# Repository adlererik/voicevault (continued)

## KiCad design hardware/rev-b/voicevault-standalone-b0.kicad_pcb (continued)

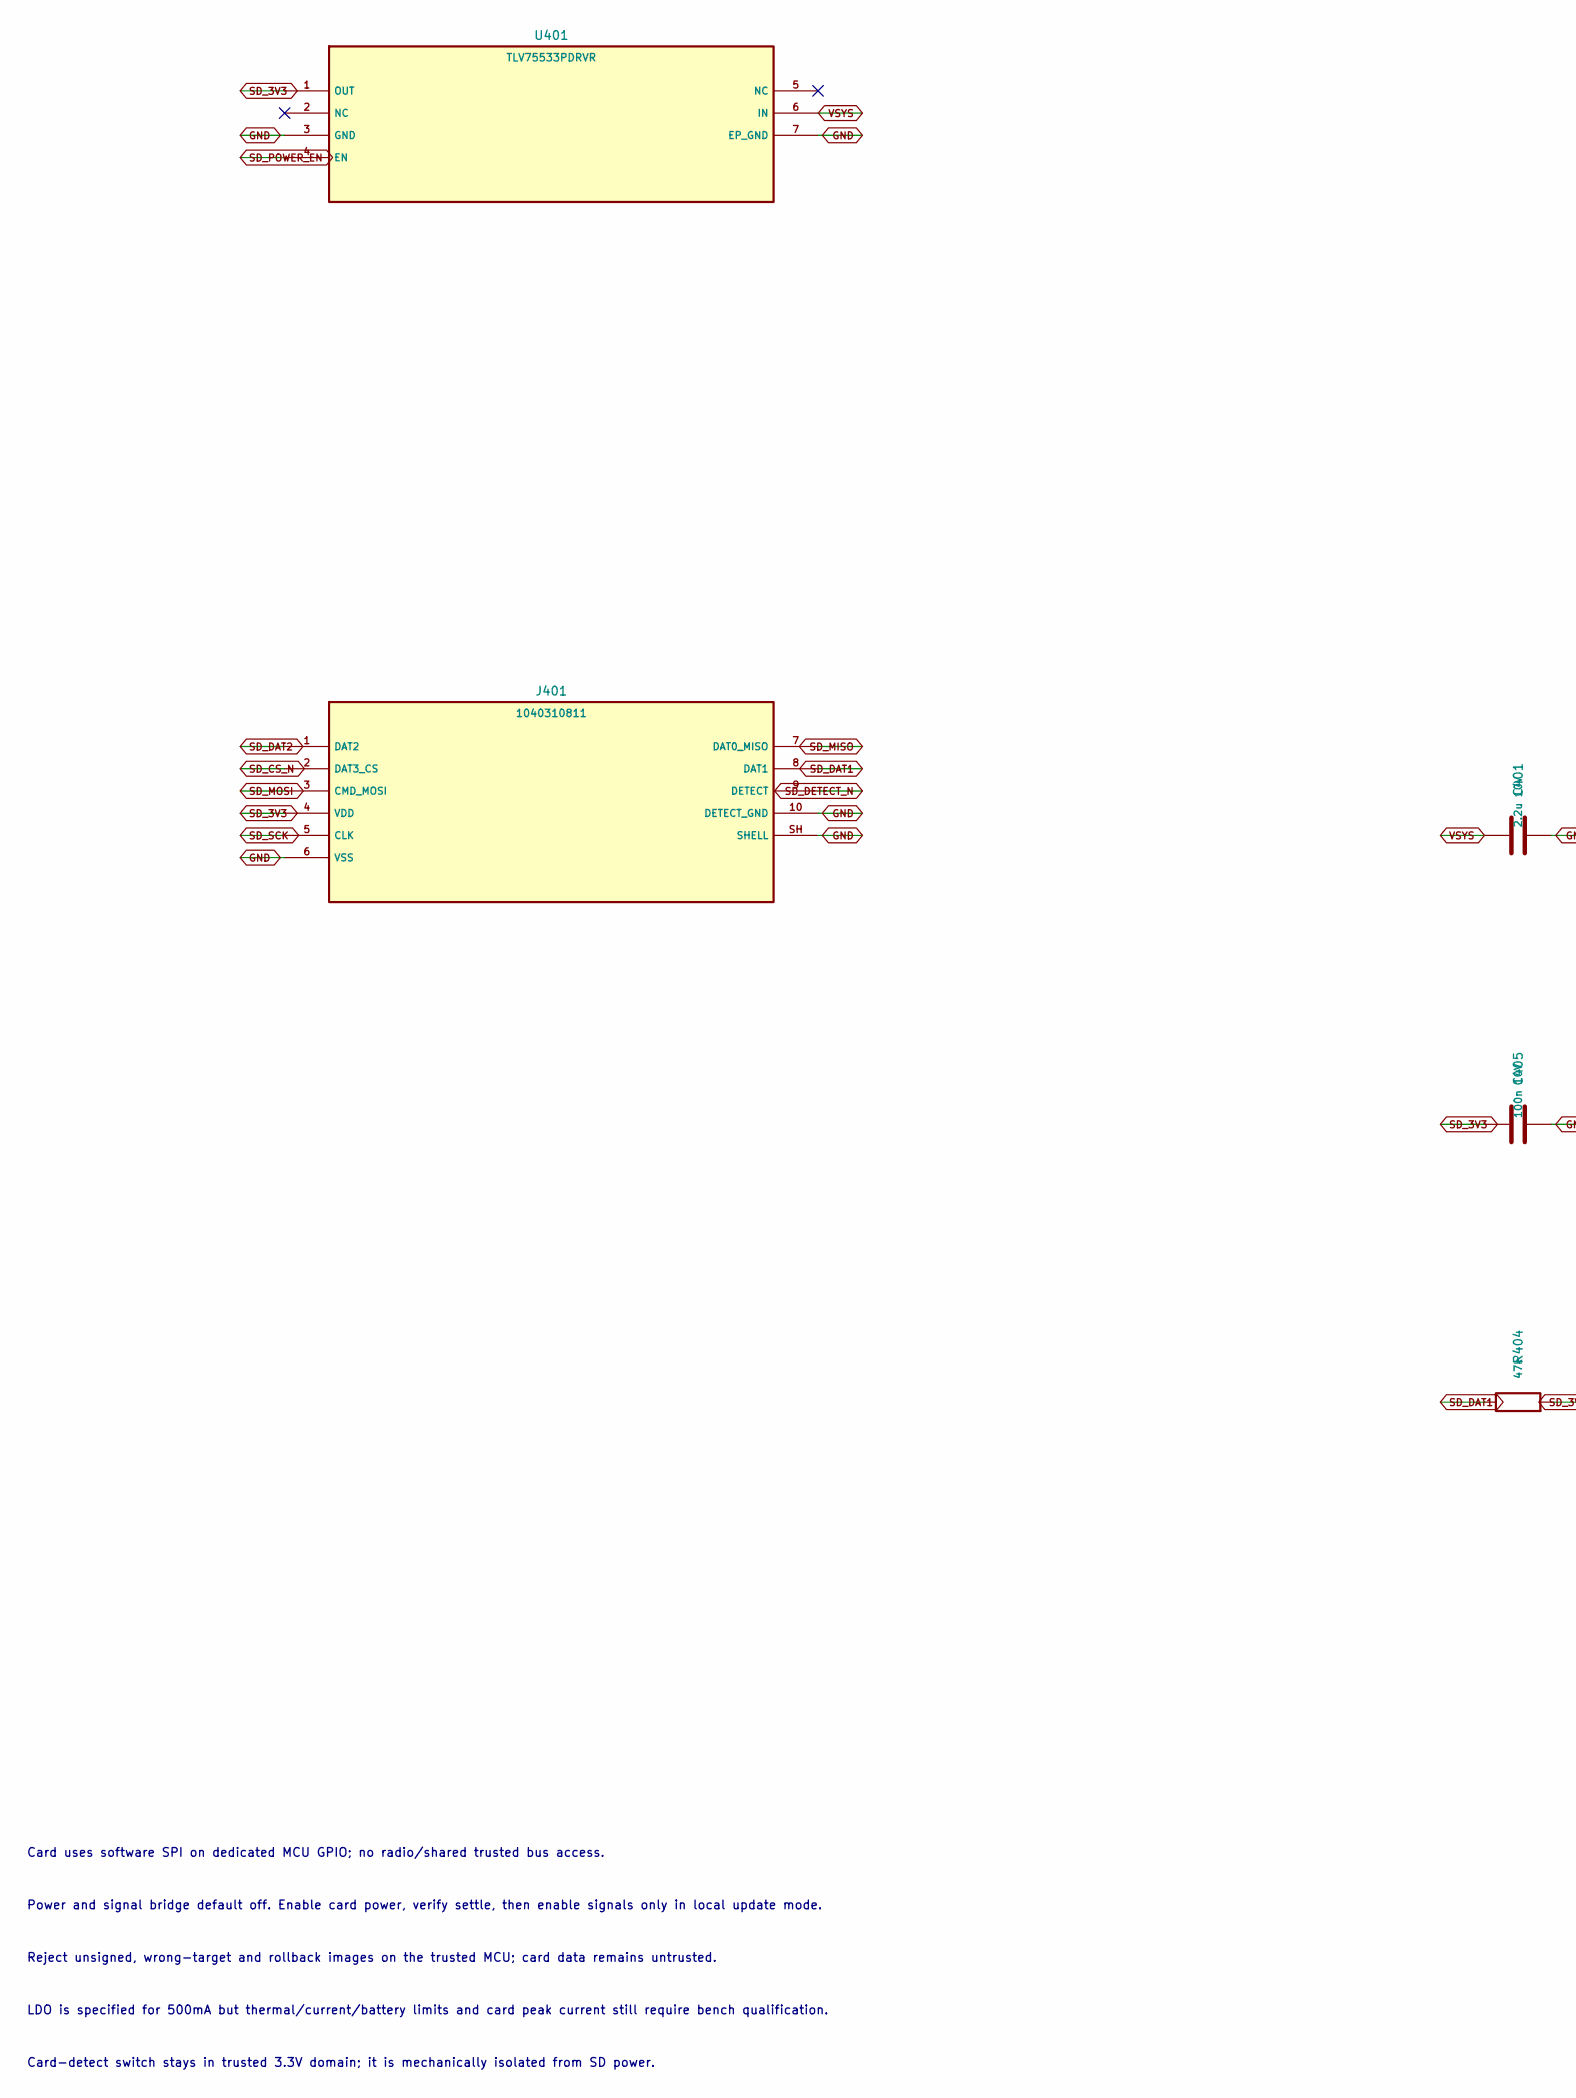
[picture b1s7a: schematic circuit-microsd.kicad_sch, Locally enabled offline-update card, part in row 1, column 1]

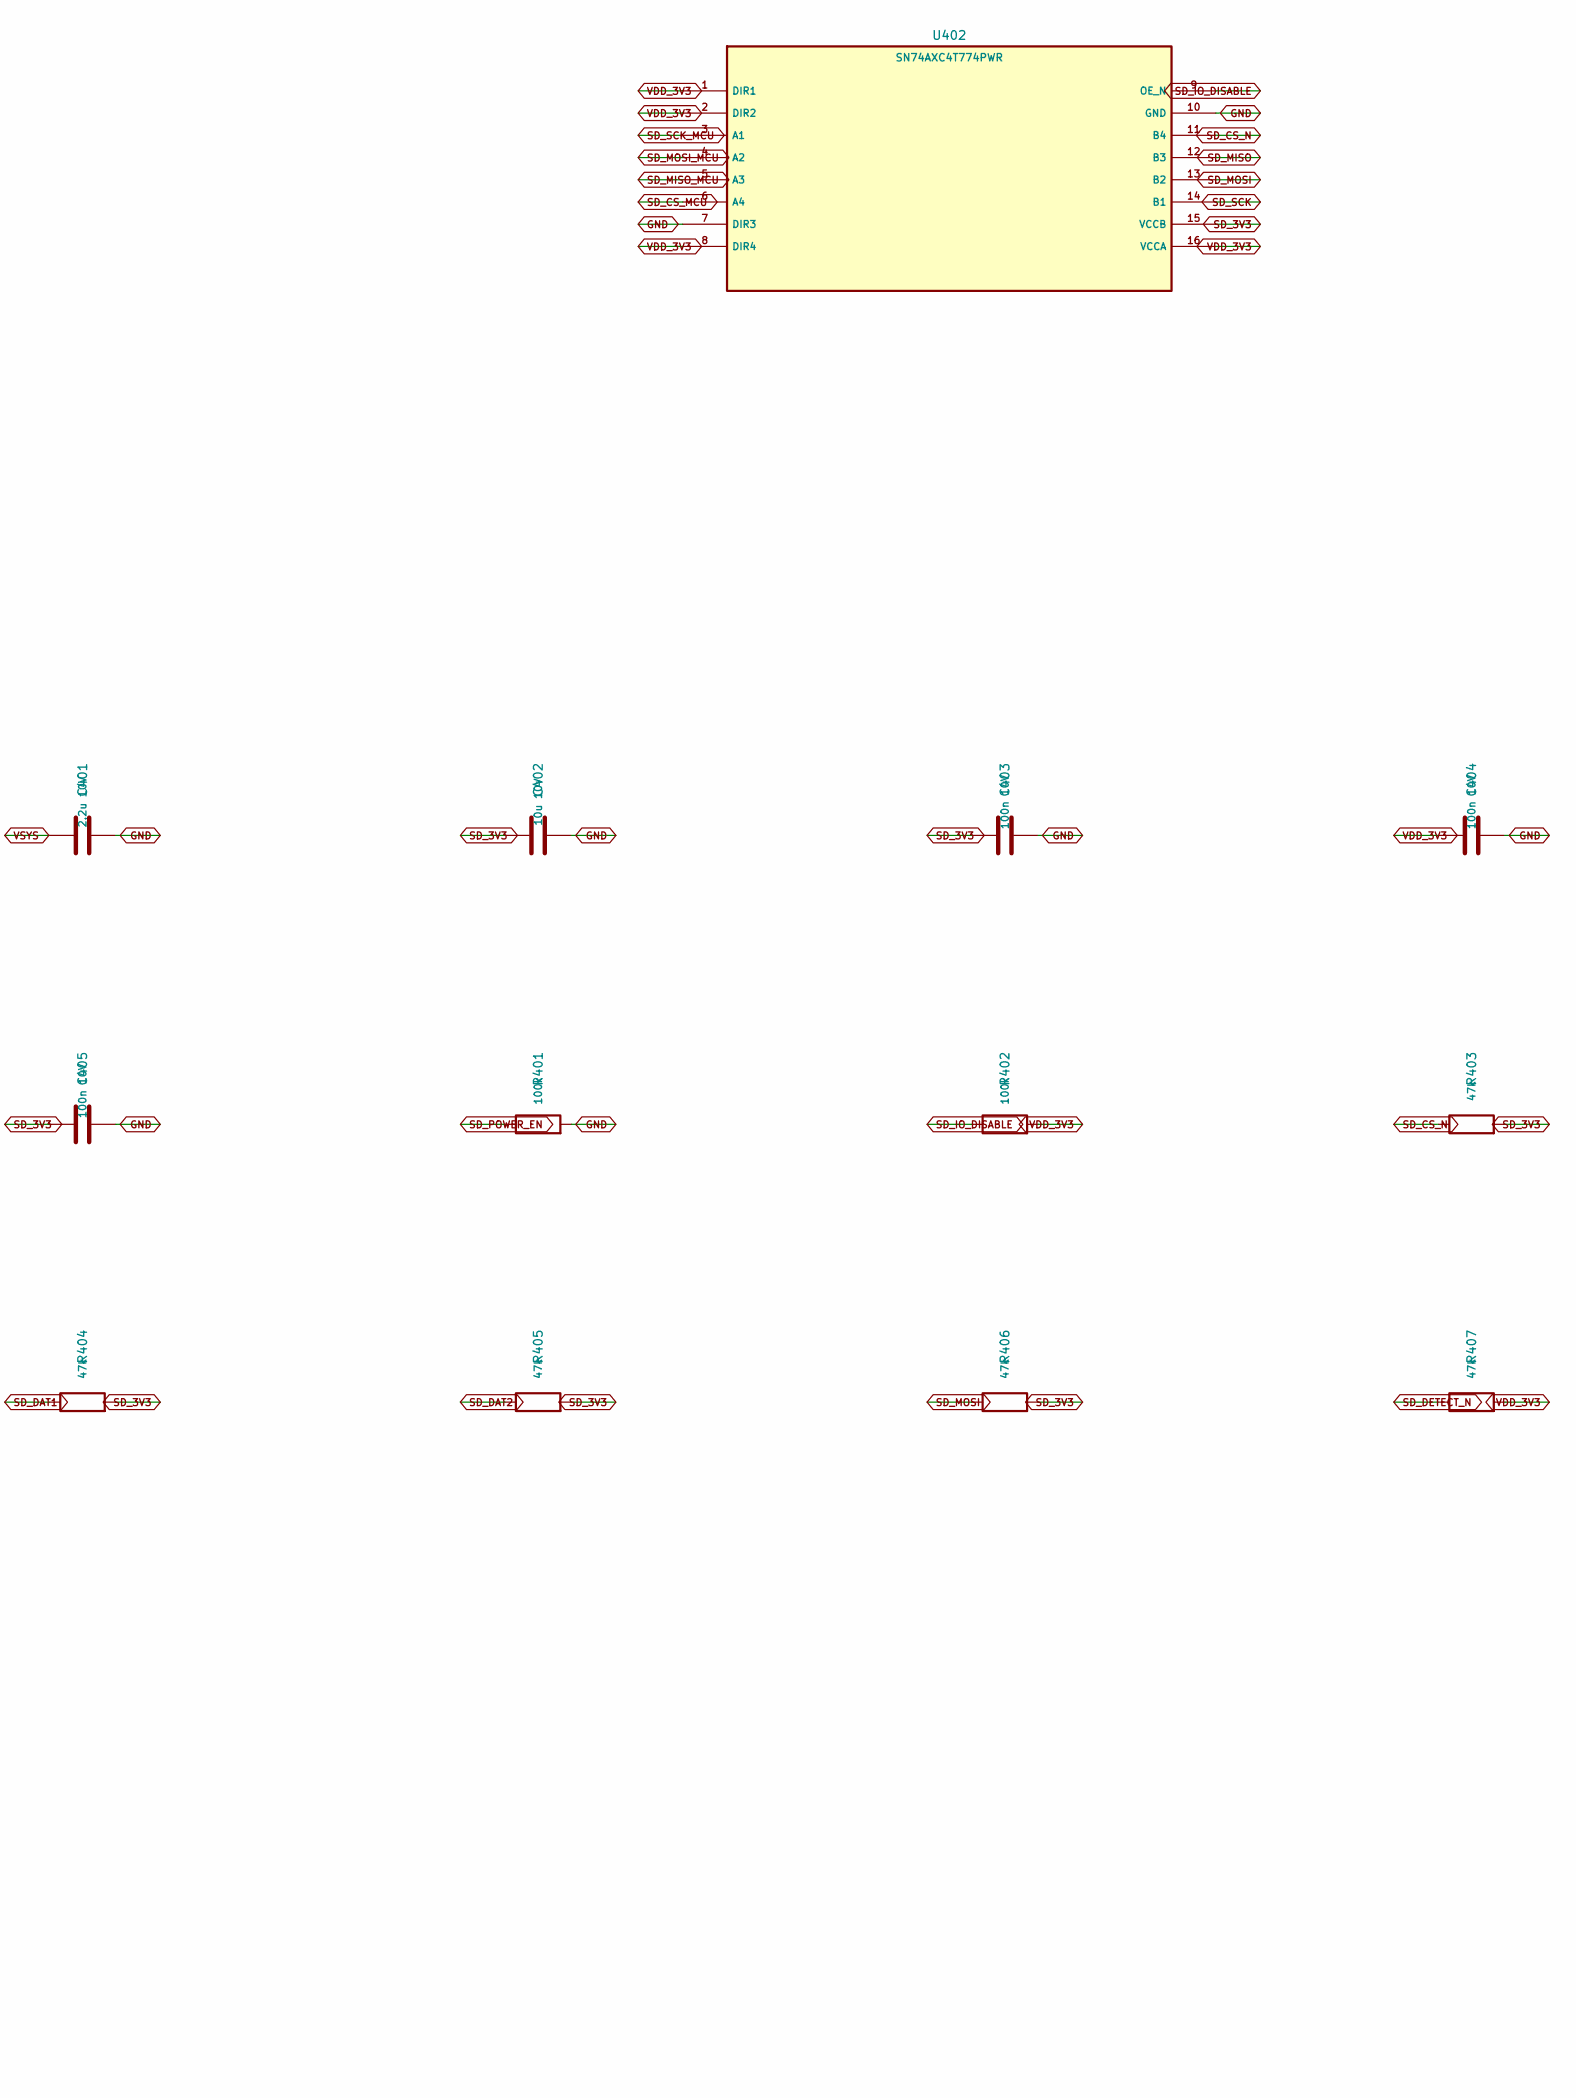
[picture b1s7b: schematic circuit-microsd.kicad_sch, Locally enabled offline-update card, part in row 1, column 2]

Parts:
C401: 2.2u 10V; C_0603_1608Metric
C402: 10u 10V; C_0805_2012Metric
C403, C404, C405: 100n 10V; C_0402_1005Metric
J401: 1040310811; microSD_HC_Molex_104031-0811
R401, R402: 100k; R_0402_1005Metric
R403, R404, R405, R406, R407: 47k; R_0402_1005Metric
U401: TLV75533PDRVR; TI_DRV0006A_WSON6_2x2_EP1x1p6
U402: SN74AXC4T774PWR; TSSOP-16_4.4x5mm_P0.65mm

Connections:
GND: C401.2, C402.2, C403.2, C404.2, C405.2, J401.6 (VSS), J401.10 (DETECT_GND), J401.SH (SHELL), R401.2, U401.3 (GND), U401.7 (EP_GND), U402.7 (DIR3), U402.10 (GND); also elsewhere on the board
SD_3V3: C402.1, C403.1, C405.1, J401.4 (VDD), R403.2, R404.2, R405.2, R406.2, U401.1 (OUT), U402.15 (VCCB); also elsewhere on the board
SD_CS_MCU: U402.6 (A4); also elsewhere on the board
SD_CS_N: J401.2 (DAT3_CS), R403.1, U402.11 (B4)
SD_DAT1: J401.8 (DAT1), R404.1
SD_DAT2: J401.1 (DAT2), R405.1
SD_DETECT_N: J401.9 (DETECT), R407.1; also elsewhere on the board
SD_IO_DISABLE: R402.1, U402.9 (OE_N); also elsewhere on the board
SD_MISO: J401.7 (DAT0_MISO), U402.12 (B3)
SD_MISO_MCU: U402.5 (A3); also elsewhere on the board
SD_MOSI: J401.3 (CMD_MOSI), R406.1, U402.13 (B2)
SD_MOSI_MCU: U402.4 (A2); also elsewhere on the board
SD_POWER_EN: R401.1, U401.4 (EN); also elsewhere on the board
SD_SCK: J401.5 (CLK), U402.14 (B1)
SD_SCK_MCU: U402.3 (A1); also elsewhere on the board
VDD_3V3: C404.1, R402.2, R407.2, U402.1 (DIR1), U402.2 (DIR2), U402.8 (DIR4), U402.16 (VCCA); also elsewhere on the board
VSYS: C401.1, U401.6 (IN); also elsewhere on the board

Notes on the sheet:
Card uses software SPI on dedicated MCU GPIO; no radio/shared trusted bus access.
Power and signal bridge default off. Enable card power, verify settle, then enable signals only in local update mode.
Reject unsigned, wrong-target and rollback images on the trusted MCU; card data remains untrusted.
LDO is specified for 500mA but thermal/current/battery limits and card peak current still require bench qualification.
Card-detect switch stays in trusted 3.3V domain; it is mechanically isolated from SD power.

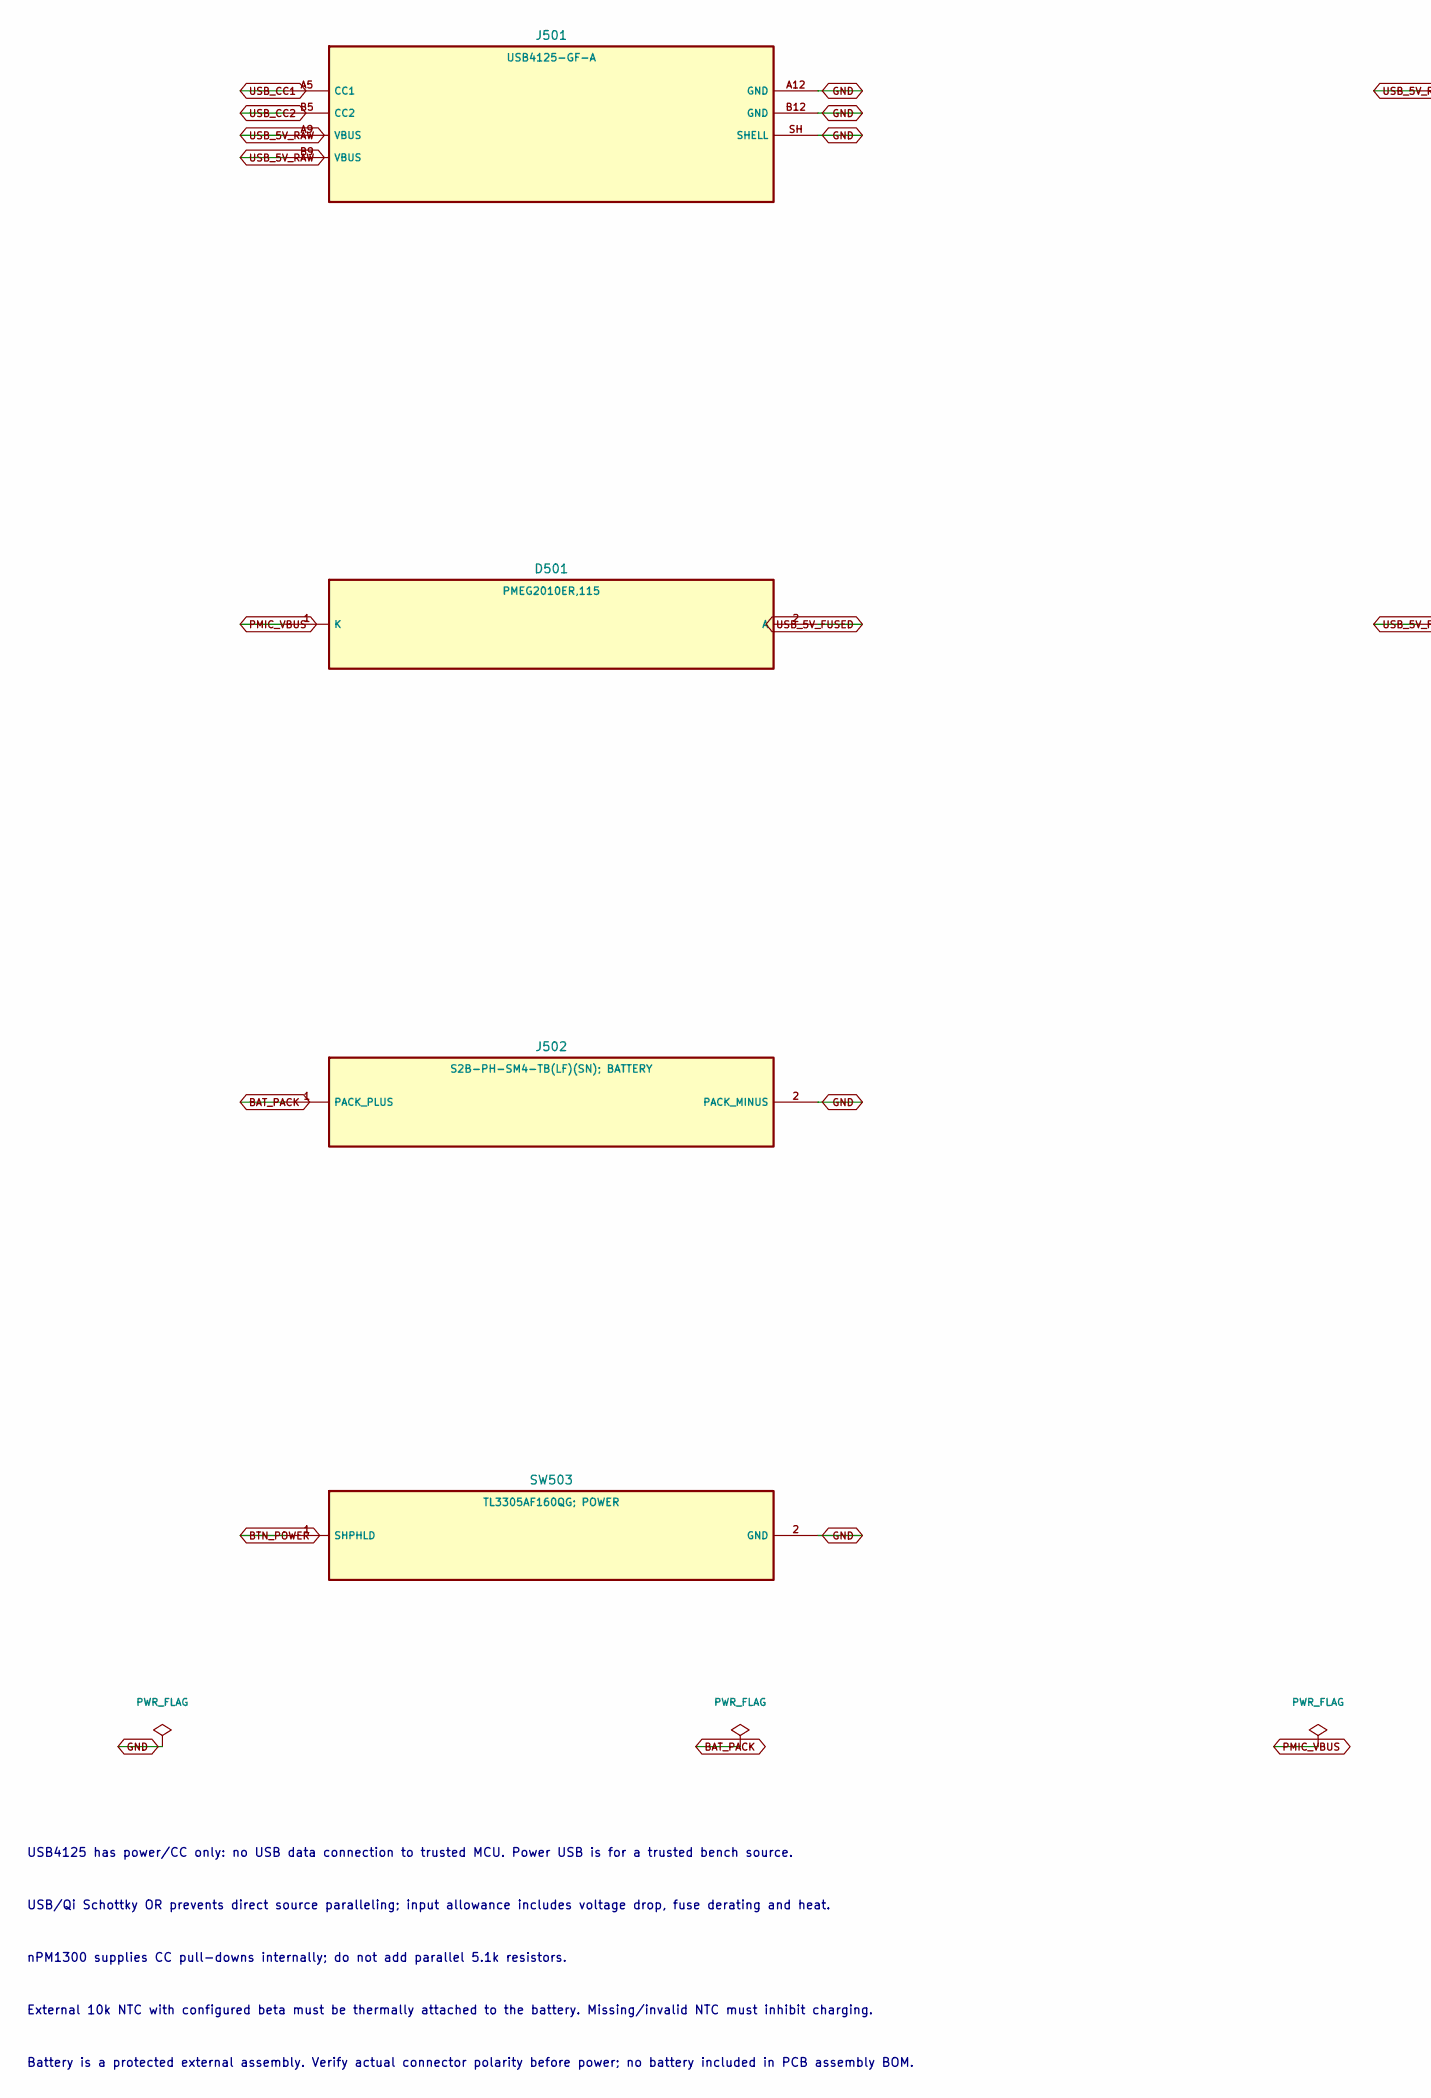
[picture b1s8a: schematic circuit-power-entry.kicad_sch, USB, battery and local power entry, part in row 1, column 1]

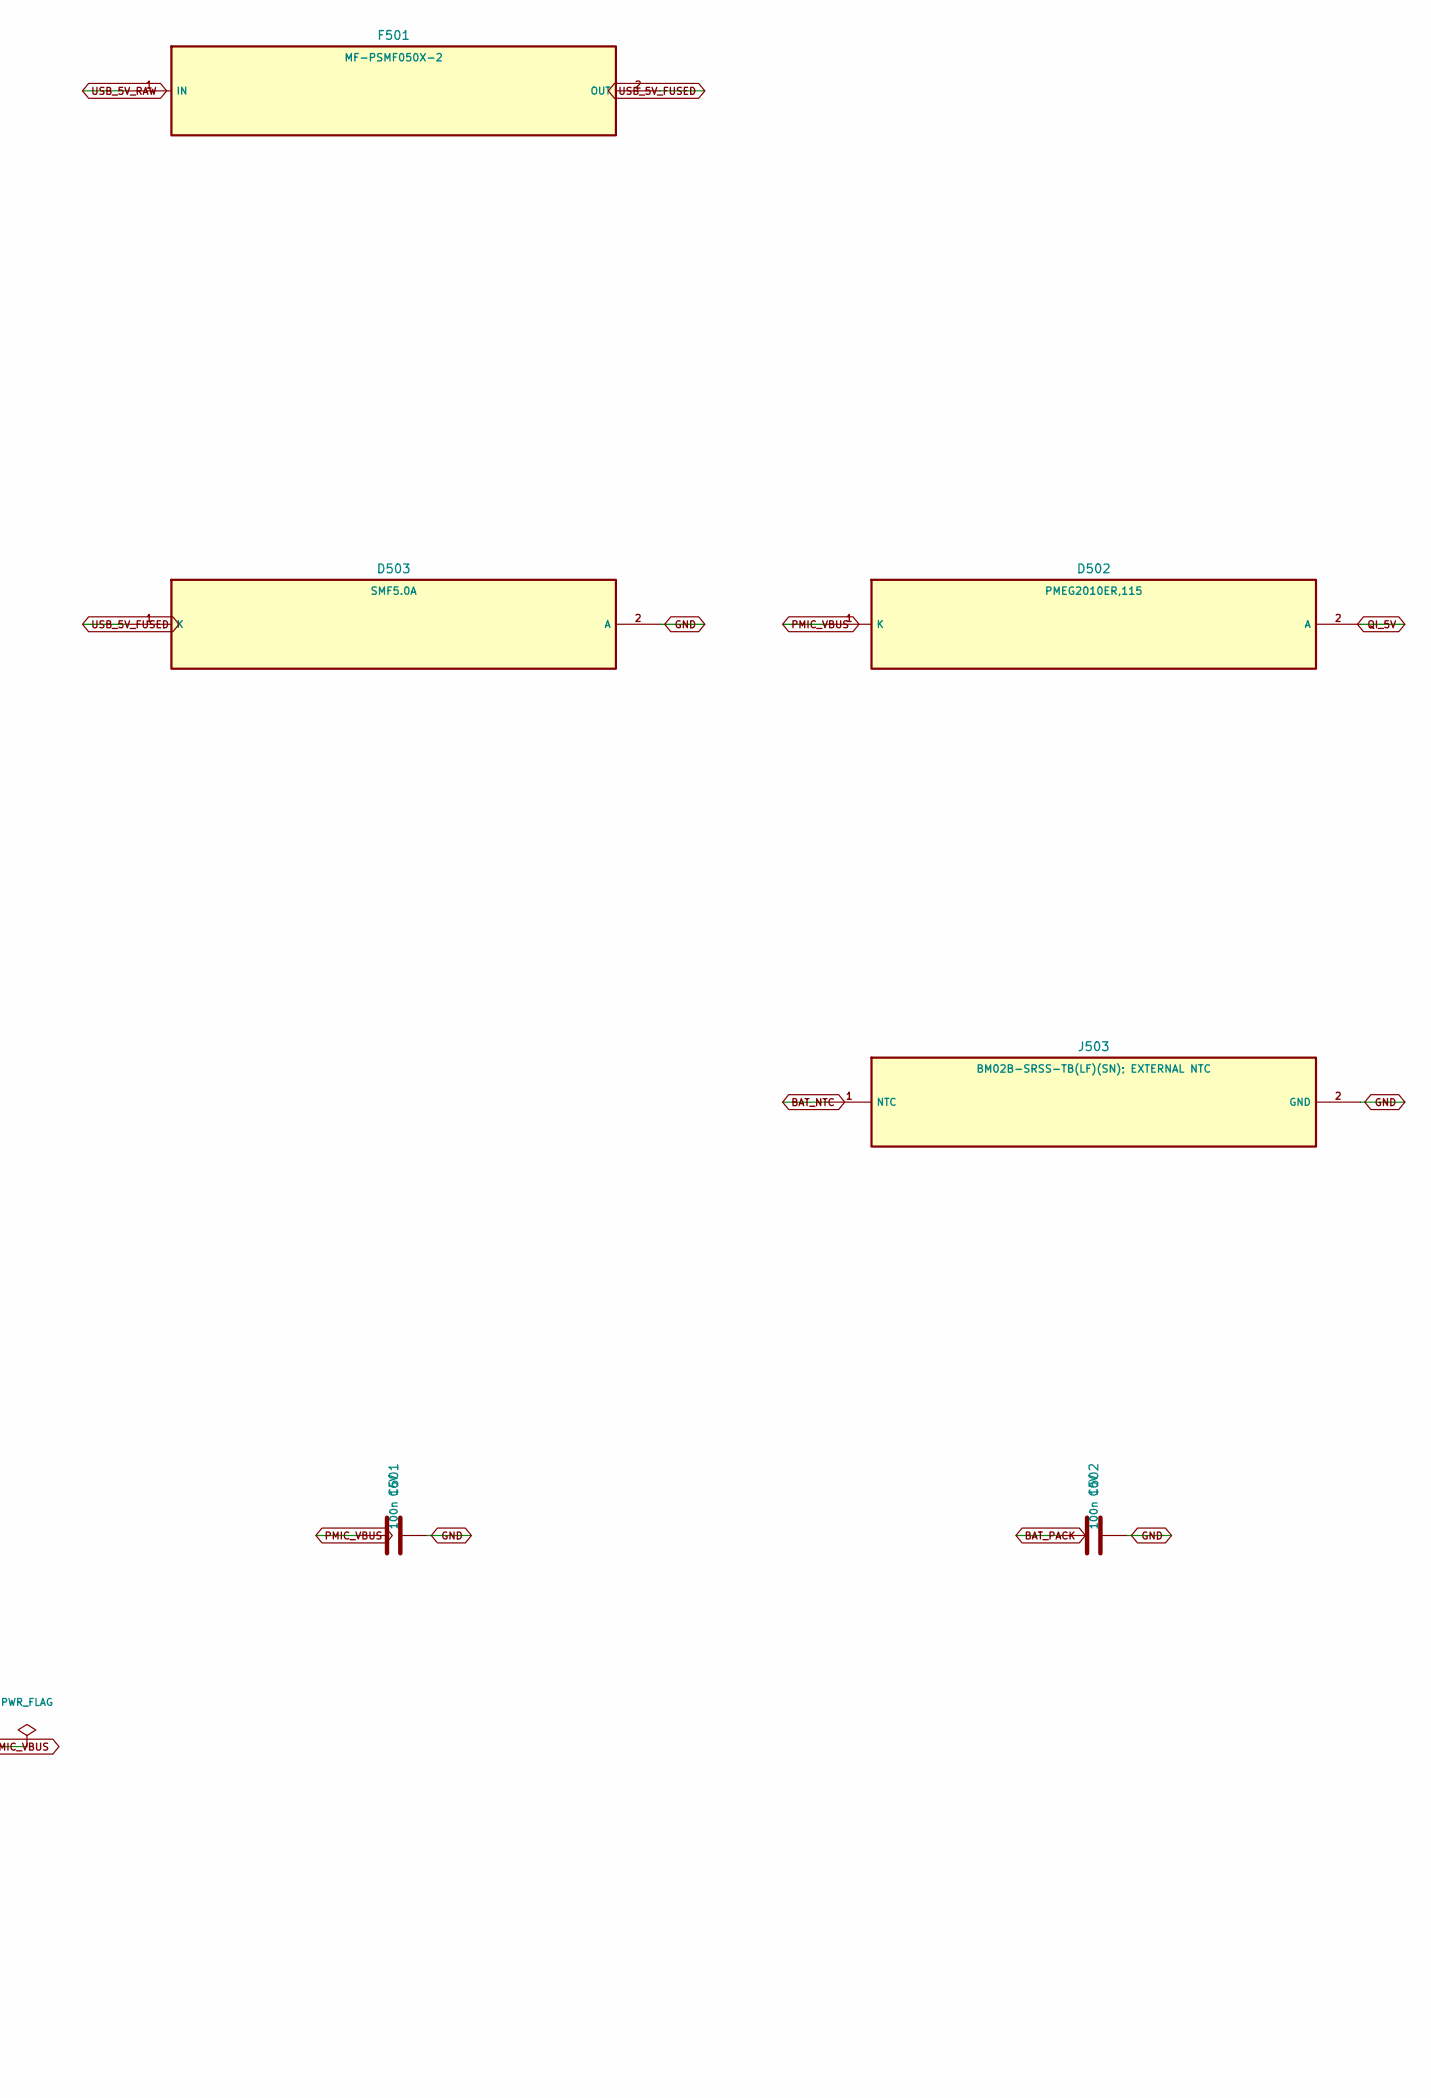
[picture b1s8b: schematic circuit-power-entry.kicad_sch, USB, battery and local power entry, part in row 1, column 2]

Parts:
C501: 100n 16V; C_0402_1005Metric
C502: 100n 10V; C_0402_1005Metric
D501, D502: PMEG2010ER,115; Nexperia_CFP3_SOD-123W
D503: SMF5.0A; D_SOD-123F
F501: MF-PSMF050X-2; Fuse_0805_2012Metric
J501: USB4125-GF-A; USB_C_Receptacle_GCT_USB4125-xx-x_6P_TopMnt_Horizontal
J502: S2B-PH-SM4-TB(LF)(SN); BATTERY; JST_PH_S2B-PH-SM4-TB_1x02-1MP_P2.00mm_Horizontal
J503: BM02B-SRSS-TB(LF)(SN); EXTERNAL NTC; JST_SH_BM02B-SRSS-TB_1x02-1MP_P1.00mm_Vertical
SW503: TL3305AF160QG; POWER; SW_SPST_TL3305A

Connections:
BAT_NTC: J503.1 (NTC); also elsewhere on the board
BAT_PACK: C502.1, J502.1 (PACK_PLUS); also elsewhere on the board
BTN_POWER: SW503.1 (SHPHLD); also elsewhere on the board
GND: C501.2, C502.2, D503.2 (A), J501.A12 (GND), J501.B12 (GND), J501.SH (SHELL), J502.2 (PACK_MINUS), J503.2 (GND), SW503.2 (GND); also elsewhere on the board
PMIC_VBUS: C501.1, D501.1 (K), D502.1 (K); also elsewhere on the board
QI_5V: D502.2 (A); also elsewhere on the board
USB_5V_FUSED: D501.2 (A), D503.1 (K), F501.2 (OUT)
USB_5V_RAW: F501.1 (IN), J501.A9 (VBUS), J501.B9 (VBUS)
USB_CC1: J501.A5 (CC1); also elsewhere on the board
USB_CC2: J501.B5 (CC2); also elsewhere on the board

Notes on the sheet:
USB4125 has power/CC only: no USB data connection to trusted MCU. Power USB is for a trusted bench source.
USB/Qi Schottky OR prevents direct source paralleling; input allowance includes voltage drop, fuse derating and heat.
nPM1300 supplies CC pull-downs internally; do not add parallel 5.1k resistors.
External 10k NTC with configured beta must be thermally attached to the battery. Missing/invalid NTC must inhibit charging.
Battery is a protected external assembly. Verify actual connector polarity before power; no battery included in PCB assembly BOM.

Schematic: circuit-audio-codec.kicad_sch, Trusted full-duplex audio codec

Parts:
C601, C602, C603, C605: 10u 10V; C_0805_2012Metric
C604, C606, C607, C608: 100n 10V; C_0402_1005Metric
D601: BAT54WS; DLDO to ALDO pop suppression; D_SOD-323
R601, R602: 2.2k; R_0402_1005Metric
R603: 100k; R_0402_1005Metric
U601: TLV320AIC3204IRHBR; QFN-32-1EP_5x5mm_P0.5mm_EP3.45x3.45mm

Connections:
AUD_ADC_DATA: U601.5 (DOUT); also elsewhere on the board
AUD_AVDD_1V8: C601.1, C607.1, D601.1 (K), U601.24 (AVDD_ALDO_OUT)
AUD_BCLK: U601.2 (BCLK); also elsewhere on the board
AUD_DAC_DATA: U601.4 (DIN); also elsewhere on the board
AUD_DVDD_1V72: C602.1, C608.1, D601.2 (A), U601.29 (DVDD_DLDO_OUT)
AUD_HPL_DC: U601.25 (HPL); also elsewhere on the board
AUD_HPR_DC: U601.27 (HPR); also elsewhere on the board
AUD_LDOIN_3V3: C605.1, C606.1, U601.26 (LDOIN_HPVDD); also elsewhere on the board
AUD_MCLK: U601.1 (MCLK); also elsewhere on the board
AUD_MICBIAS: U601.19 (MICBIAS); also elsewhere on the board
AUD_REF: C603.1, U601.18 (REF)
AUD_RESET_N: R603.1, U601.31 (RESET_N); also elsewhere on the board
AUD_SCL: R601.1, U601.9 (SCL); also elsewhere on the board
AUD_SDA: R602.1, U601.10 (SDA); also elsewhere on the board
AUD_WCLK: U601.3 (WCLK); also elsewhere on the board
GND: C601.2, C602.2, C603.2, C604.2, C605.2, C606.2, C607.2, C608.2, R603.2, U601.7 (IOVSS), U601.8 (SCLK_MFP3), U601.12 (SPI_SELECT_I2C), U601.17 (AVSS), U601.28 (DVSS), U601.33 (EP_GND); also elsewhere on the board
MIC_ADC: U601.13 (IN1_L); also elsewhere on the board
VDD_3V3: C604.1, R601.2, R602.2, U601.6 (IOVDD), U601.30 (LDO_SELECT_INTERNAL); also elsewhere on the board

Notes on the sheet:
TI SLOS602E pins/package; SLAA492A internal DLDO/ALDO sequence with DVDD-to-AVDD Schottky diode.
IOVDD uses VDD_3V3; LDOIN has a separate switched 500mA-capable regulator. LDO_SELECT high enables internal 1.72V DLDO; AVDD/DVDD are not tied to 3.3V.
Hold RESET low while rails settle; wait at least 1ms after reset before writes, enable ALDO at >=DLDO voltage, then ADC/DAC.
SAI1 AF13: PE2 MCLK_A, PE3 SD_B capture, PE4 FS_A, PE5 SCK_A, PE6 SD_A playback.
Audio I2C2 PF0/PF1 and SAI are connected only to the trusted MCU; no radio wires.

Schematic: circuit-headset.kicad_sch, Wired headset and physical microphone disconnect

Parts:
C609: 1u 10V X7R; C_0603_1608Metric
C610: 33p C0G; C_0402_1005Metric
C611, C612: 220u 6.3V polymer; exact MPN qualification pending; CP_EIA-7343-31_Kemet-D
D602, D603, D604: PESD5V0S1BA,115; bidirectional ESD; D_SOD-323
J601: SJ-43514-SMT-TR; CTIA headset; SJ43514SMT
R604: 2.2k 1%; R_0402_1005Metric
R605: 1k 1%; R_0402_1005Metric
R606, R607: 10R 1% 0.1W; R_0402_1005Metric
SW601: JS102011SAQN; physical microphone disconnect; SW_SPDT_CK_JS102011SAQN

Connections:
AUD_HPL_DC: C611.1 (PLUS); also elsewhere on the board
AUD_HPR_DC: C612.1 (PLUS); also elsewhere on the board
AUD_MICBIAS: R604.1; also elsewhere on the board
GND: C610.2, D602.2 (RETURN), D603.2 (RETURN), D604.2 (RETURN), J601.4 (RING2_GND), SW601.3 (MUTE_GROUND); also elsewhere on the board
HEADSET_L: D602.1 (LINE), J601.2 (TIP_LEFT), R606.2
HEADSET_MIC: D604.1 (LINE), J601.1 (SLEEVE_MIC), SW601.1 (TALK)
HEADSET_R: D603.1 (LINE), J601.3 (RING1_RIGHT), R607.2
HP_L_AC: C611.2 (MINUS), R606.1
HP_R_AC: C612.2 (MINUS), R607.1
MIC_ADC: C609.2, C610.1; also elsewhere on the board
MIC_BIASED: R604.2, R605.1, SW601.2 (COMMON)
MIC_COUPLE: C609.1, R605.2

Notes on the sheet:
CTIA only: Tip L, ring1 R, ring2 GND, sleeve MIC. OMTP requires an external passive adapter.
Mute switch disconnects headset microphone and grounds codec-side input; bias is after the disconnect.
No built-in microphone or speaker. Headphone outputs are independently AC coupled; never short HPL/HPR together.
220u coupling and 10R series values are evaluated in SPICE; exact capacitor MPN and headset/audio quality need qualification.
ESD parts are protective design elements, not a claim of tested IEC immunity.

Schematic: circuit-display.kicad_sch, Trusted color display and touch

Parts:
C701: 4.7u 10V; C_0603_1608Metric
C702: 100n 10V; C_0402_1005Metric
C703: 1u 10V; C_0603_1608Metric
J701: FH12-40S-0.5SH(55); TFT FFC; Hirose_FH12-40S-0.5SH_1x40-1MP_P0.50mm_Horizontal
J702: 2005280060; TOUCH FFC; Molex_200528-0060_1x06-1MP_P1.00mm_Horizontal
R701, R702: 4.7k; R_0402_1005Metric
R703, R704: 100k; R_0402_1005Metric
R705, R706: 47k; R_0402_1005Metric

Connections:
BL_ANODE: J701.38 (LED_A); also elsewhere on the board
BL_K1: J701.34 (LED_K1); also elsewhere on the board
BL_K2: J701.35 (LED_K2); also elsewhere on the board
BL_K3: J701.36 (LED_K3); also elsewhere on the board
BL_K4: J701.37 (LED_K4); also elsewhere on the board
GND: C701.2, C702.2, C703.2, J701.1 (GND), J701.12 (WRX_UNUSED), J701.13 (RDX_UNUSED), J701.14 (DB0), J701.15 (DB1), J701.16 (DB2), J701.17 (DB3), J701.18 (DB4), J701.19 (DB5), J701.20 (DB6), J701.21 (DB7), J701.22 (DB8), J701.23 (DB9), J701.24 (DB10), J701.25 (DB11), J701.26 (DB12), J701.27 (DB13), J701.28 (DB14), J701.29 (DB15), J701.33 (GND), J701.39 (GND), J702.2 (VSS), R703.2, R704.2; also elsewhere on the board
LCD_CS_N: J701.10 (CSX), R705.1; also elsewhere on the board
LCD_RESET_N: J701.30 (RESX), R703.1; also elsewhere on the board
LCD_SCK: J701.11 (DCX_SCL); also elsewhere on the board
LCD_SDI: J701.9 (SDA); also elsewhere on the board
LCD_SDO: J701.6 (SDO); also elsewhere on the board
LCD_TE: J701.40 (TE); also elsewhere on the board
TOUCH_IRQ_N: J702.5 (INT_N), R706.1; also elsewhere on the board
TOUCH_RESET_N: J702.6 (RESET_N), R704.1; also elsewhere on the board
TOUCH_SCL: J702.3 (SCL), R701.1; also elsewhere on the board
TOUCH_SDA: J702.4 (SDA), R702.1; also elsewhere on the board
VDD_3V3: C701.1, C702.1, C703.1, J701.7 (VDD), J701.8 (VDDI), J701.31 (IM0_SPI), J701.32 (IM2_SPI), J702.1 (VDD), R701.2, R702.2, R705.2, R706.2; also elsewhere on the board

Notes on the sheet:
Newhaven NHD-2.4-240320AF-CTXP-CTP: 3-wire, 9-bit SPI3; IM0/IM2 high. Unused WR/RD/DB grounded per module wiring diagram.
IOVDD/LCD/touch use trusted MCU rail; hold both resets low until firmware confirms 3.3V.
Touch uses I2C5 PD0/PD1 AF4, separate from power, audio and secure-element buses.
Connector equivalents are bottom-contact 40x0.5mm and 6x1.0mm. Verify actual flex thickness, pin-1 and bend clearance.
Display is a separately procured assembly, not an IC mounted by the board assembler.

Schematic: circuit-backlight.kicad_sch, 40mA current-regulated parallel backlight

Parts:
C704: 2.2u 10V; C_0603_1608Metric
C705: 1u 50V X7R; C_0805_2012Metric
D701: BZT52H-C6V2,115; open-load clamp; D_SOD-123F
L701: SRN4018-220M / 22uH; L_Bourns-SRN4018
R707: 12R 1% 0.1W; R_0402_1005Metric
R708: 100k; R_0402_1005Metric
R709, R710, R711, R712: 200R 1% 0.25W; R_0805_2012Metric
U9: TPS61062YZFR; TPS61062_YZF8_REVIEW

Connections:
BACKLIGHT_PWM: R708.1, U9.A2 (EN); also elsewhere on the board
BL_ANODE: C705.1, D701.1 (K), U9.C1 (OUT); also elsewhere on the board
BL_FB: D701.2 (A), R707.1, R709.2, R710.2, R711.2, R712.2, U9.B3 (FB)
BL_K1: R709.1; also elsewhere on the board
BL_K2: R710.1; also elsewhere on the board
BL_K3: R711.1; also elsewhere on the board
BL_K4: R712.1; also elsewhere on the board
BL_SW: L701.2, U9.C2 (SW)
GND: C704.2, C705.2, R707.2, R708.2, U9.A1 (GND), U9.A3 (ILED_500mV), U9.C3 (PGND); also elsewhere on the board
VSYS: C704.1, L701.1, U9.B1 (VIN); also elsewhere on the board

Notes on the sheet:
TPS61062 constant-current mode: ILED grounded, 0.5V / 12R = 41.7mA nominal total; tolerance minimum 40.0mA.
Four 200R / 0.25W ballast resistors share branch current; include zener-clamp and open-LED fault sensitivity.
Boost input is VSYS directly; its worst-case current exceeds the PMIC load-switch 100mA rating. AUX buck budget remains a gate.
PWM at <=1kHz, default-low EN. Initial total backlight current is approximately 42mA.
6.2V zener provides alternate feedback path on open load; output capacitor is rated 50V for device OVP.
YZF land-pattern geometry still needs exact manufacturer package-drawing review; do not release fabrication.
Input is raw VSYS (2.7-6V driver range), with full operation gated at VSYS >=3.6V pending bench qualification; do not use the MCU/AUX buck for boost input.

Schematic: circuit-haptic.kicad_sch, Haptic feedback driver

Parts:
C801, C802: 100n 10V; C_0402_1005Metric
C803: 10u 10V; C_0805_2012Metric
J801: BM02B-SRSS-TB(LF)(SN); LRA; JST_SH_BM02B-SRSS-TB_1x02-1MP_P1.00mm_Vertical
R801: 100k; R_0402_1005Metric
R802: 47k; R_0402_1005Metric
U10: DRV2624YFFR; DRV2624_YFF9

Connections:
GND: C801.2, C802.2, C803.2, R801.2, U10.B3 (GND); also elsewhere on the board
HAPTIC_IRQ_N: R802.1, U10.A1 (TRIG_INT_N); also elsewhere on the board
HAPTIC_MINUS: J801.2 (LRA_MINUS), U10.C3 (OUT_MINUS)
HAPTIC_PLUS: J801.1 (LRA_PLUS), U10.A3 (OUT_PLUS)
HAPTIC_REG: C802.1, U10.A2 (REG)
HAPTIC_RESET_N: R801.1, U10.B2 (NRST); also elsewhere on the board
PMIC_SCL: U10.C1 (SCL); also elsewhere on the board
PMIC_SDA: U10.B1 (SDA); also elsewhere on the board
VDD_3V3: R802.2; also elsewhere on the board
VSYS: C801.1, C803.1, U10.C2 (VDD); also elsewhere on the board

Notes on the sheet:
DRV2624 9-ball YFF map and 0.225mm pad / 0.4mm pitch from TI SLOS893D package drawing.
Actuator is an external LRA assembly. Its exact MPN, rated drive and auto-calibration settings remain qualification gates.
NRST defaults low; no startup vibration. Use I2C address 0x5A on trusted power-control bus.

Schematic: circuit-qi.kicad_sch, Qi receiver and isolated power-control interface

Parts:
C901, C902: 100n 50V X7R; C_0805_2012Metric
C903: 47n 50V X7R; C_0805_2012Metric
C904: 1n 50V C0G; C_0603_1608Metric
C905, C906: 47n 50V; C_0603_1608Metric
C907, C908: 22n 50V; C_0603_1608Metric
C909, C910: 10n 50V; C_0603_1608Metric
C911: 4.7u 10V; C_0603_1608Metric
C912: 1u 10V; C_0603_1608Metric
C913, C914, C915, C916: 10u 25V X5R; C_0805_2012Metric
C917, C918: 100n 25V; C_0603_1608Metric
D903, D904: SMF13A; D_SOD-123F
J901: BM02B-SRSS-TB(LF)(SN); 760308101219 COIL; JST_SH_BM02B-SRSS-TB_1x02-1MP_P1.00mm_Vertical
R907, R908: ERJ-P08F2000V / 200R surge; R_1206_3216Metric
U5: STWLC38JRM; STWLC38_WLCSP40_REVIEW

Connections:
GND: C911.2, C912.2, C913.2, C914.2, C915.2, C916.2, C917.2, C918.2, D903.2 (A), D904.2 (A), U5.A1 (VSSP), U5.A2 (VSSP), U5.A4 (VSSP), U5.A5 (VSSP), U5.E5 (VSSA), U5.F5 (VSSD); also elsewhere on the board
QI_5V: C915.1, C916.1, C917.1, U5.E1 (VOUT), U5.E2 (VOUT_PARALLEL); also elsewhere on the board
QI_AC1: C901.2, C902.2, C903.2, C904.1, C905.2, C907.2, C909.2, D903.1 (K), U5.B4 (AC1), U5.B5 (AC1), U5.C4 (AC1), U5.C5 (AC1)
QI_AC2: C904.2, C906.2, C908.2, C910.2, D904.1 (K), J901.2 (COIL_B), U5.B1 (AC2), U5.B2 (AC2), U5.C1 (AC2), U5.C2 (AC2)
QI_BOOT1: C905.1, U5.B3 (BOOT1)
QI_BOOT2: C906.1, U5.C3 (BOOT2)
QI_COIL_A: C901.1, C902.1, C903.1, J901.1 (COIL_A); also elsewhere on the board
QI_COMA1: C907.1, U5.G1 (COMA1)
QI_COMA2: C908.1, U5.G2 (COMA2)
QI_COMB1: C909.1, U5.H1 (COMB1)
QI_COMB2: C910.1, U5.H2 (COMB2)
QI_ENB: U5.G4 (ENB); also elsewhere on the board
QI_IEXT: R907.2, R908.2, U5.A3 (IEXT)
QI_IRQ_N: U5.H4 (INTB); also elsewhere on the board
QI_NTC: U5.F1 (NTC); also elsewhere on the board
QI_SCL: U5.H5 (SCL); also elsewhere on the board
QI_SDA: U5.G5 (SDA); also elsewhere on the board
QI_VAA_2V5: C911.1, U5.E4 (VAA); also elsewhere on the board
QI_VDD_1V1: C912.1, U5.F4 (VDD)
QI_VRECT: C913.1, C914.1, C918.1, R907.1, R908.1, U5.D1 (VRECT), U5.D2 (VRECT), U5.D3 (VRECT), U5.D4 (VRECT), U5.D5 (VRECT)
QI_VS: U5.F2 (VS); also elsewhere on the board

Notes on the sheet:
ST DS14078 Rev1 Table37 wearable reference; catalogue coil 760308101219 (11.8uH), 247n series, 1n parallel.
Qi I2C is software-driven on PD3/PD4, physically separate from PMIC/secure-element buses. Bound every transaction and timeout.
Configure and read back 5.0V RX output; no reverse-transmit mode. nPM1300 input OVP rejects excessive output voltage.
See Qi sensing/control sheet for separate control bus, thermistor and ASK filter.
Coil/charger/metal-stack tuning, FOD, thermal, surge and layout qualification are still required.

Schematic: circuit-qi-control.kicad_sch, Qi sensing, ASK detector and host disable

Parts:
C919: 3.3n 50V; C_0603_1608Metric
C920: 22n 50V; C_0603_1608Metric
C921: 1.5n 50V; C_0603_1608Metric
C922: 1n 10V; C_0402_1005Metric
D901, D902: 1N4148WS-7-F; D_SOD-323
J902: BM02B-SRSS-TB(LF)(SN); COIL NTC; JST_SH_BM02B-SRSS-TB_1x02-1MP_P1.00mm_Vertical
Q901: AO3401A (AOS); SOT-23
Q902: 2N7002; SOT-23
R901, R904: 10k 1%; R_0402_1005Metric
R902: 6.8k 1%; R_0402_1005Metric
R903: 220k 1%; R_0402_1005Metric
R905: 150k 1%; R_0402_1005Metric
R906: 100k 1%; R_0402_1005Metric
R909, R910: 2.2k; R_0402_1005Metric
R911: 47k; R_0402_1005Metric
R912, R913, R914: 100k; R_0402_1005Metric

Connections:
GND: C919.2, C921.2, C922.2, D902.2 (A), J902.2 (RETURN), Q902.2 (S), R903.2, R906.2, R913.2, R914.2; also elsewhere on the board
QI_COIL_A: D901.2 (A); also elsewhere on the board
QI_DEMOD_COUPLE: C920.1, R904.2
QI_DEMOD_FILTER: C919.1, R902.2, R903.1, R904.1
QI_DEMOD_RAW: D901.1 (K), R902.1
QI_DISABLE: Q902.1 (G), R914.1; also elsewhere on the board
QI_ENB: Q901.3 (D), R913.1; also elsewhere on the board
QI_EN_GATE: Q901.1 (G), Q902.3 (D), R912.1
QI_IRQ_N: R911.1; also elsewhere on the board
QI_NTC: C922.1, J902.1 (10k_NTC), R901.2; also elsewhere on the board
QI_SCL: R909.1; also elsewhere on the board
QI_SDA: R910.1; also elsewhere on the board
QI_VAA_2V5: Q901.2 (S), R901.1, R905.1, R912.2; also elsewhere on the board
QI_VS: C920.2, C921.1, D902.1 (K), R905.2, R906.1; also elsewhere on the board
VDD_3V3: R909.2, R910.2, R911.2; also elsewhere on the board

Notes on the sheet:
Qi control bus is separate from PMIC and secure-element buses; bound transactions and timeouts.
NTC must be attached to the coil. Divider and actual thermal cutoff must be bench-qualified.
Two-FET ENB circuit defaults to autonomous startup and avoids driving an unpowered chip from the MCU rail.
ASK detector follows ST DS14078 Figure15; 1N4148WS substitutes the reference signal diode and needs bench comparison.
